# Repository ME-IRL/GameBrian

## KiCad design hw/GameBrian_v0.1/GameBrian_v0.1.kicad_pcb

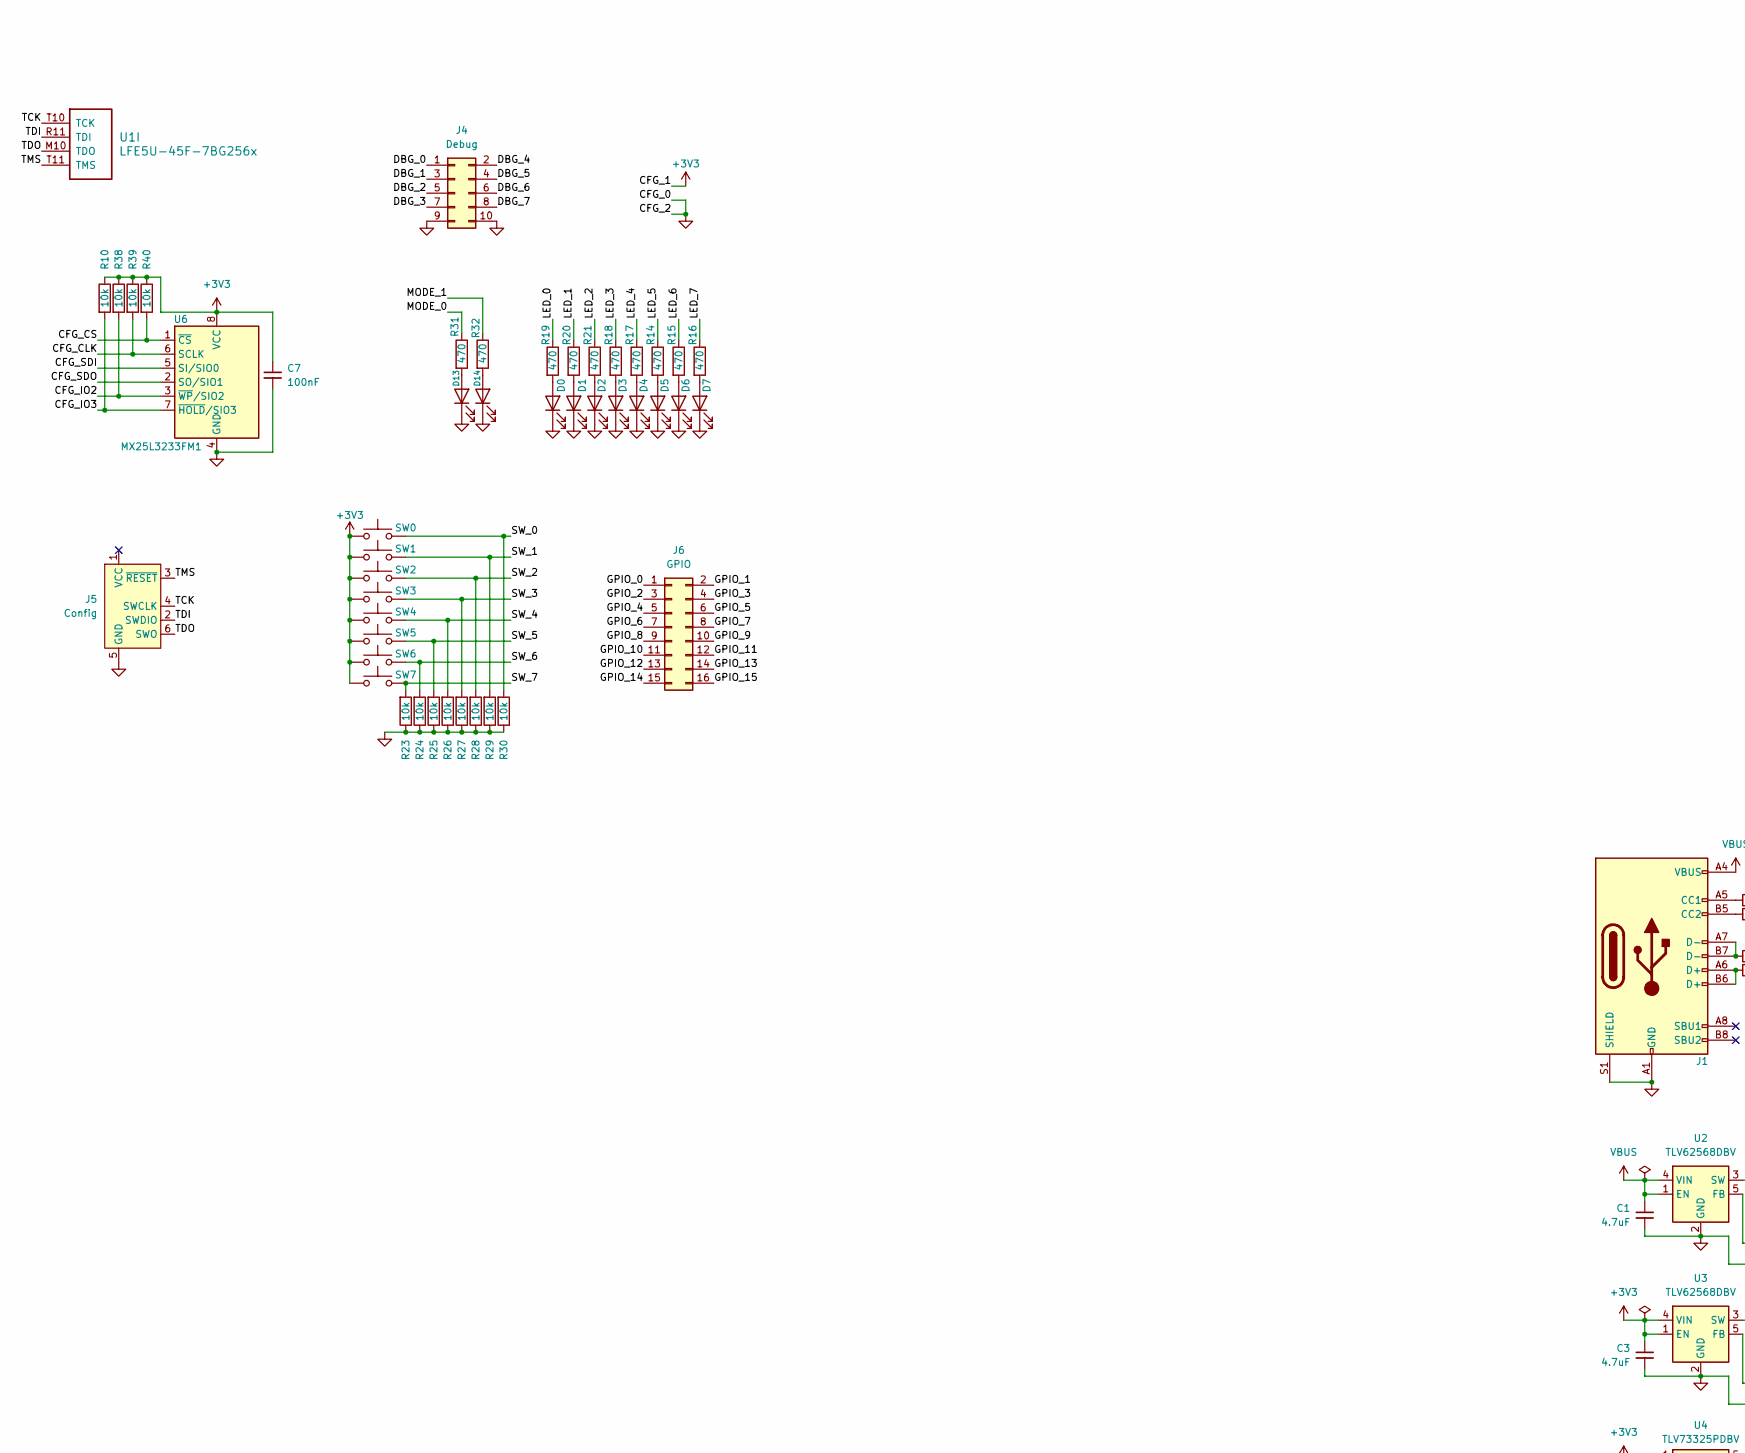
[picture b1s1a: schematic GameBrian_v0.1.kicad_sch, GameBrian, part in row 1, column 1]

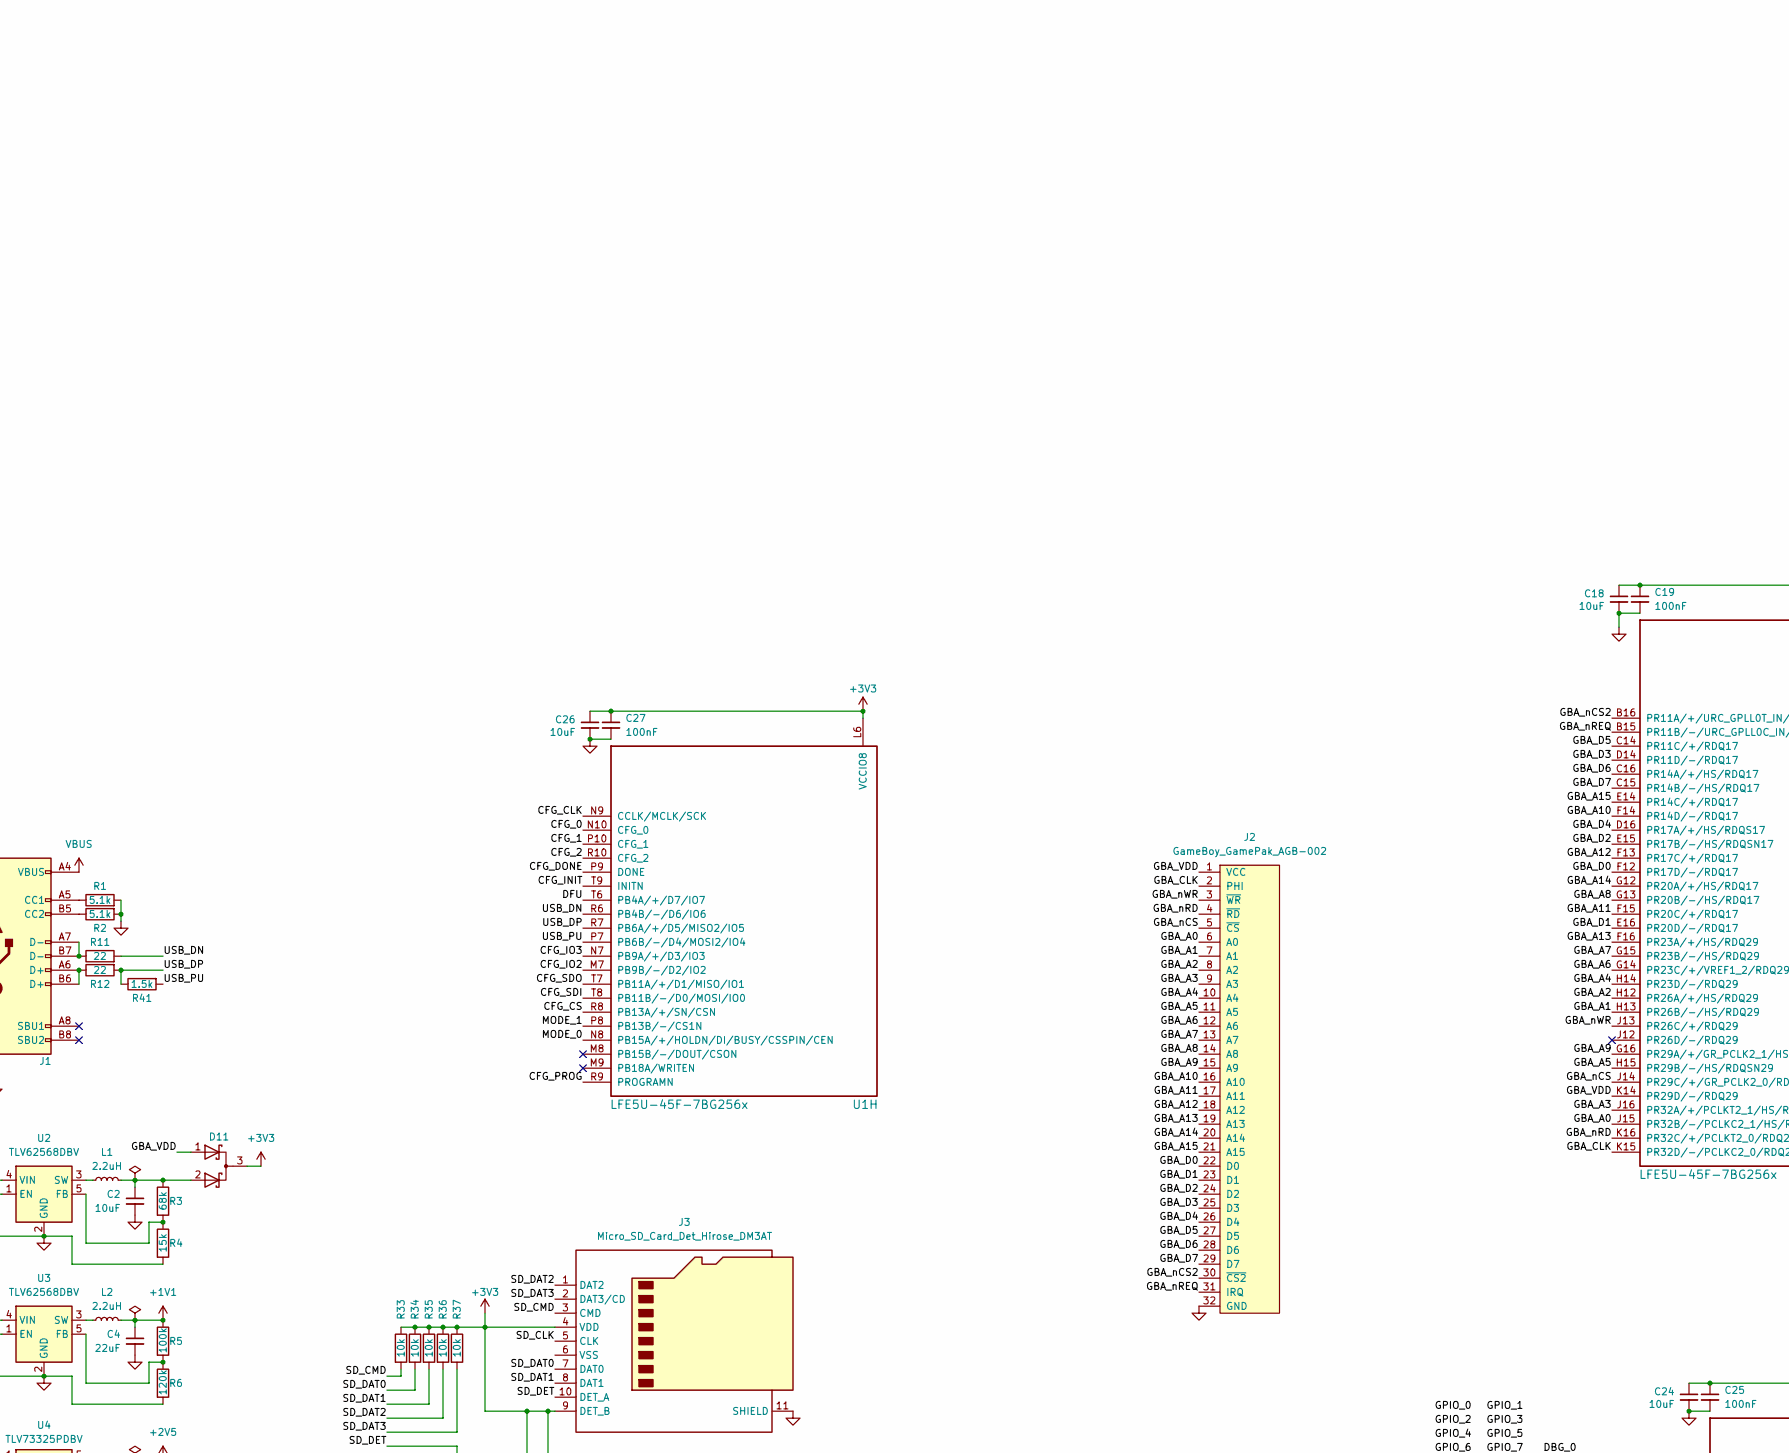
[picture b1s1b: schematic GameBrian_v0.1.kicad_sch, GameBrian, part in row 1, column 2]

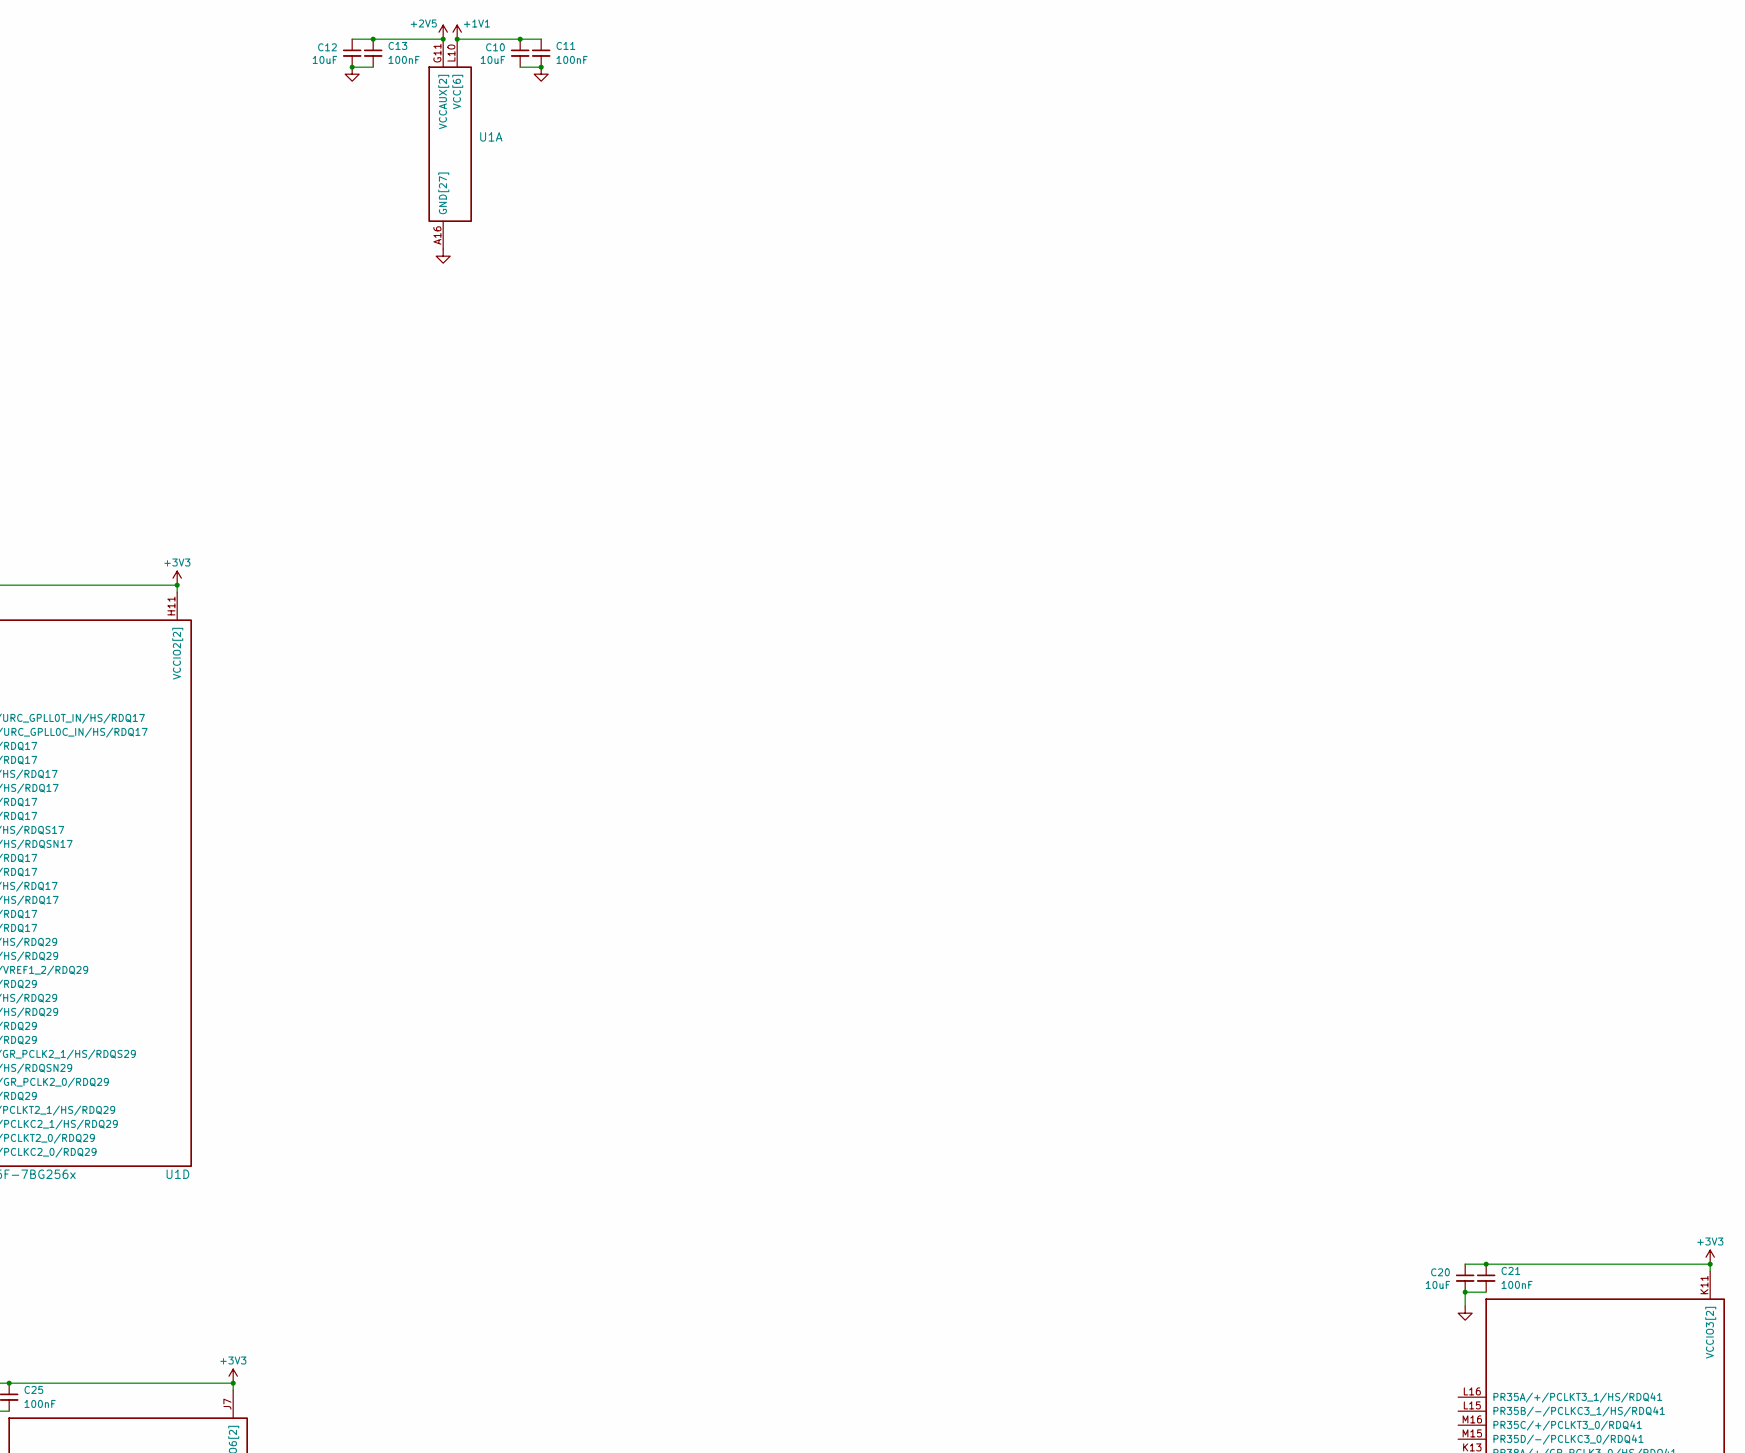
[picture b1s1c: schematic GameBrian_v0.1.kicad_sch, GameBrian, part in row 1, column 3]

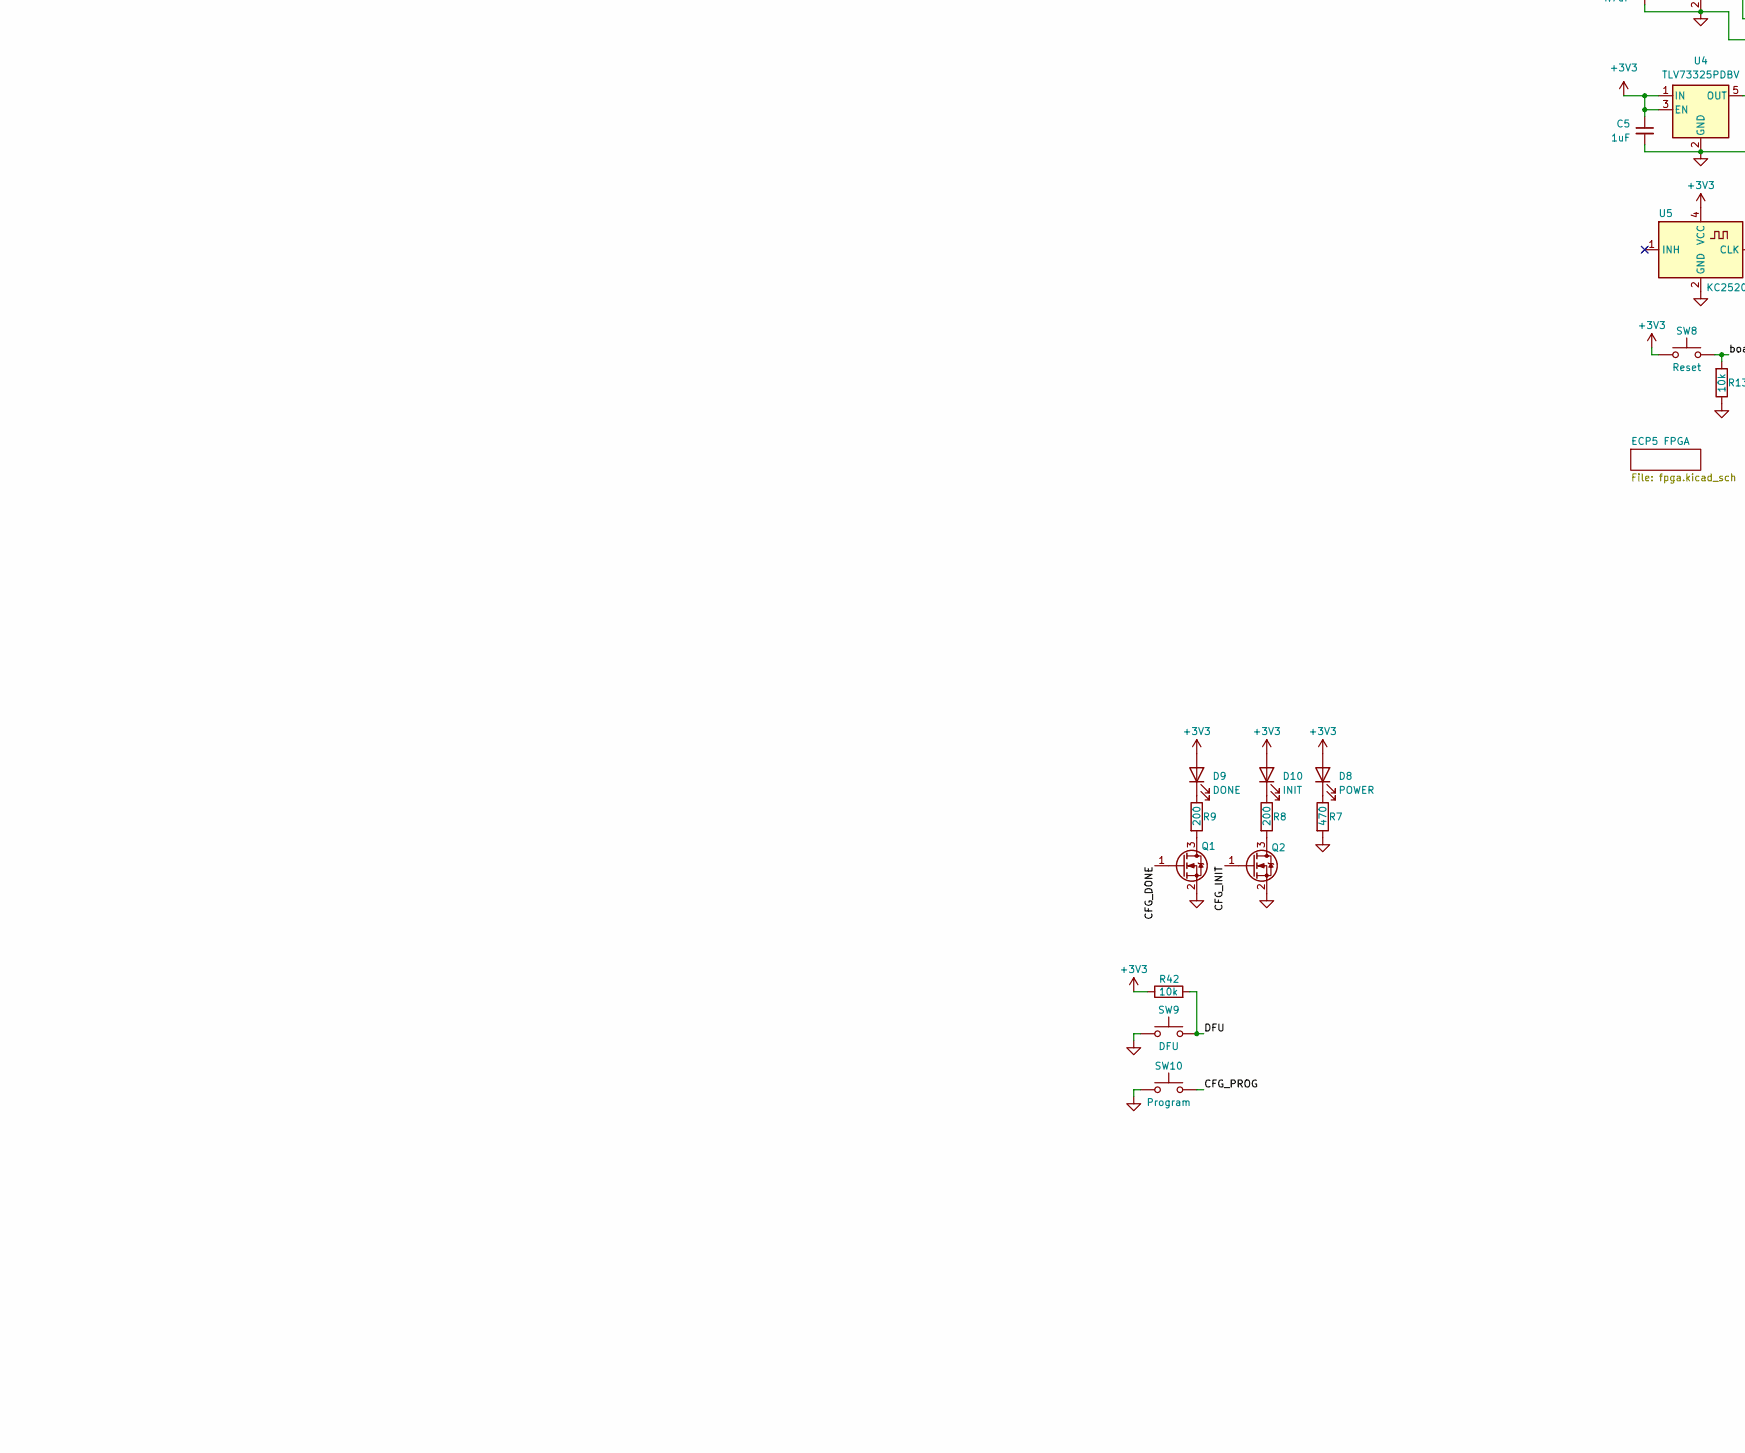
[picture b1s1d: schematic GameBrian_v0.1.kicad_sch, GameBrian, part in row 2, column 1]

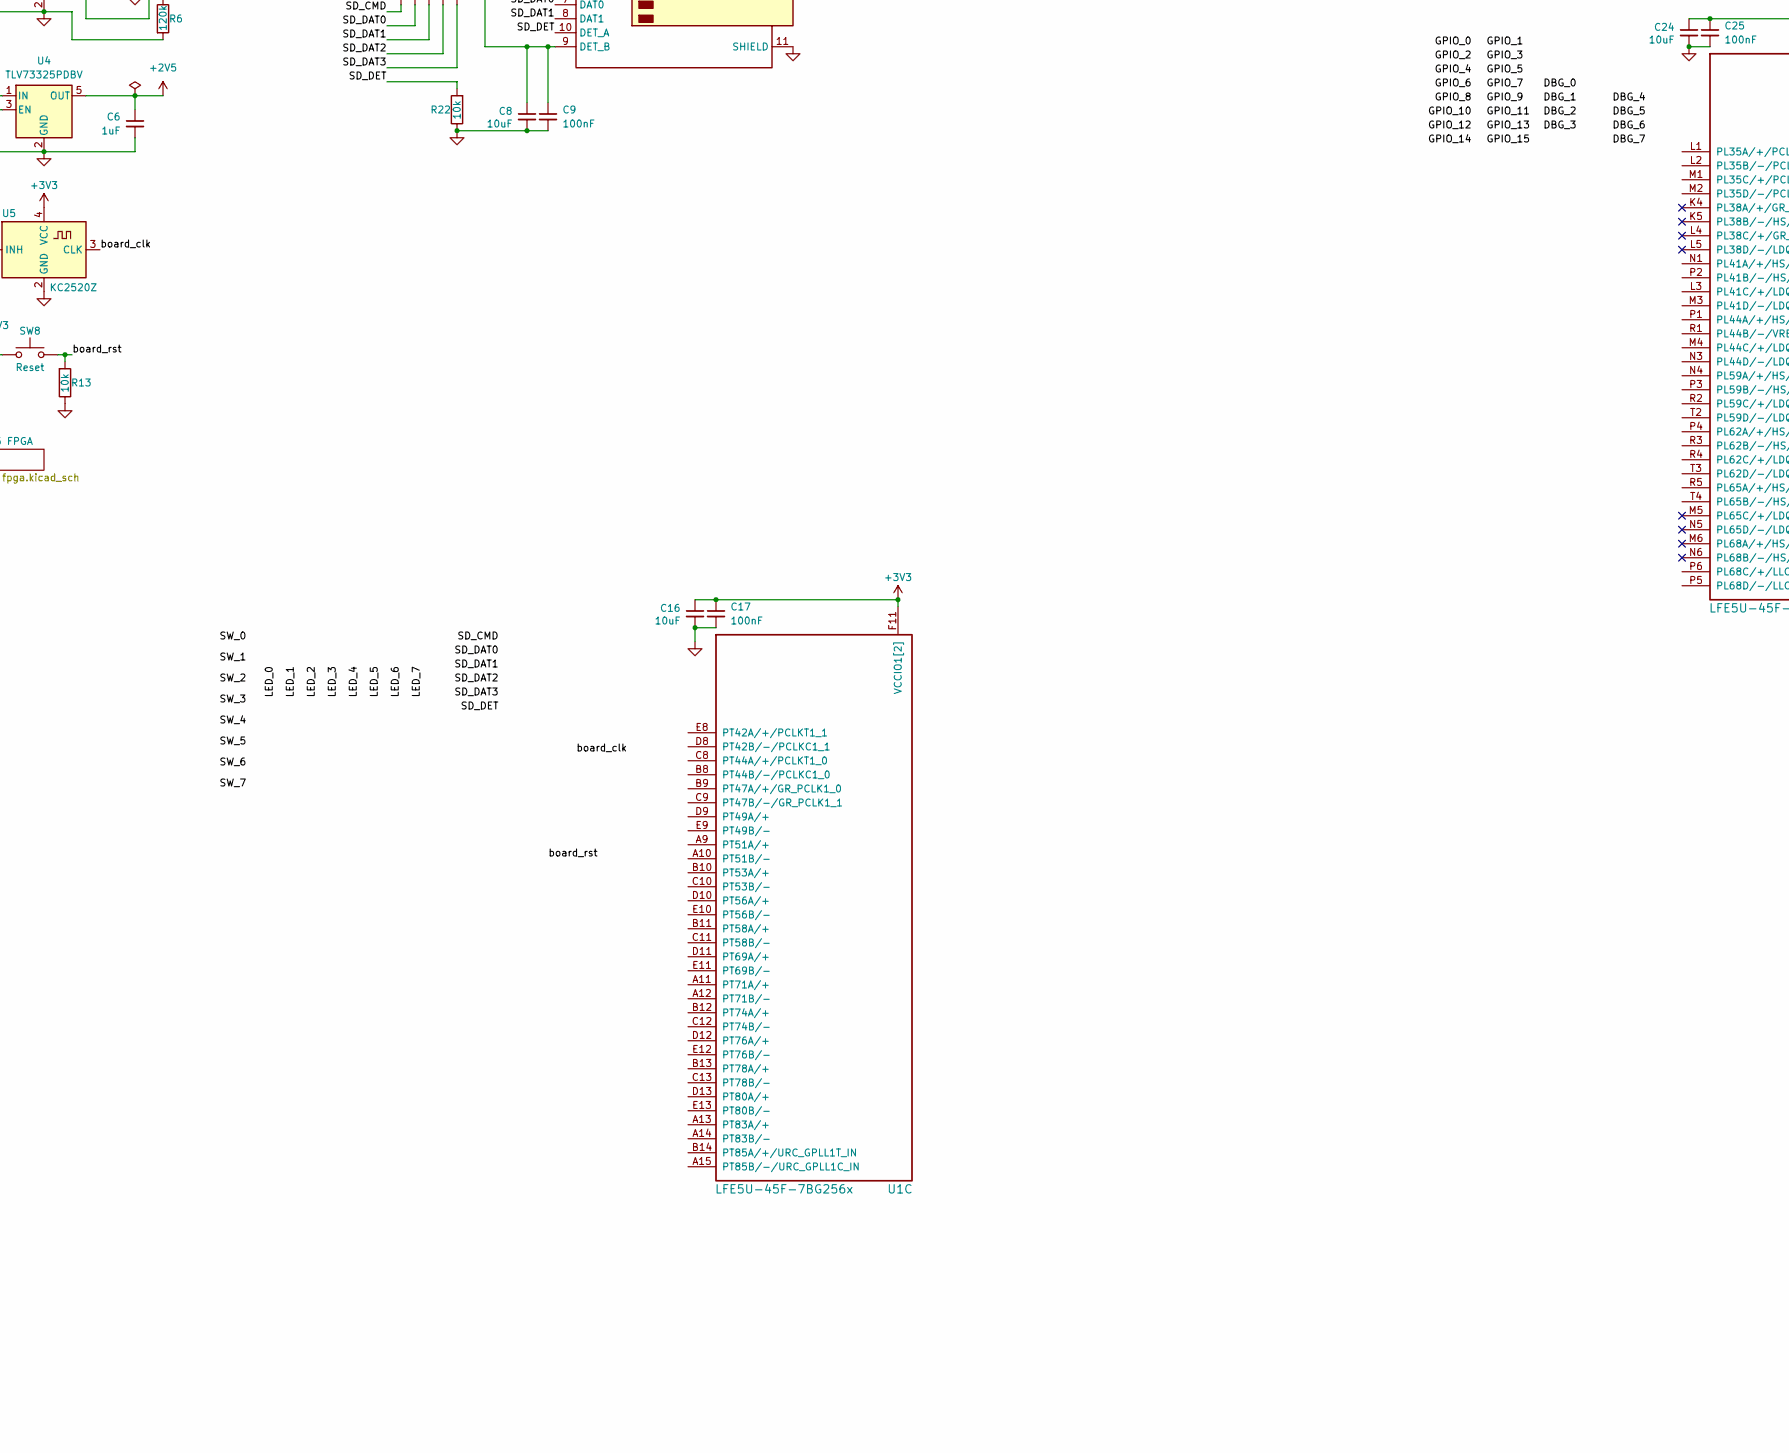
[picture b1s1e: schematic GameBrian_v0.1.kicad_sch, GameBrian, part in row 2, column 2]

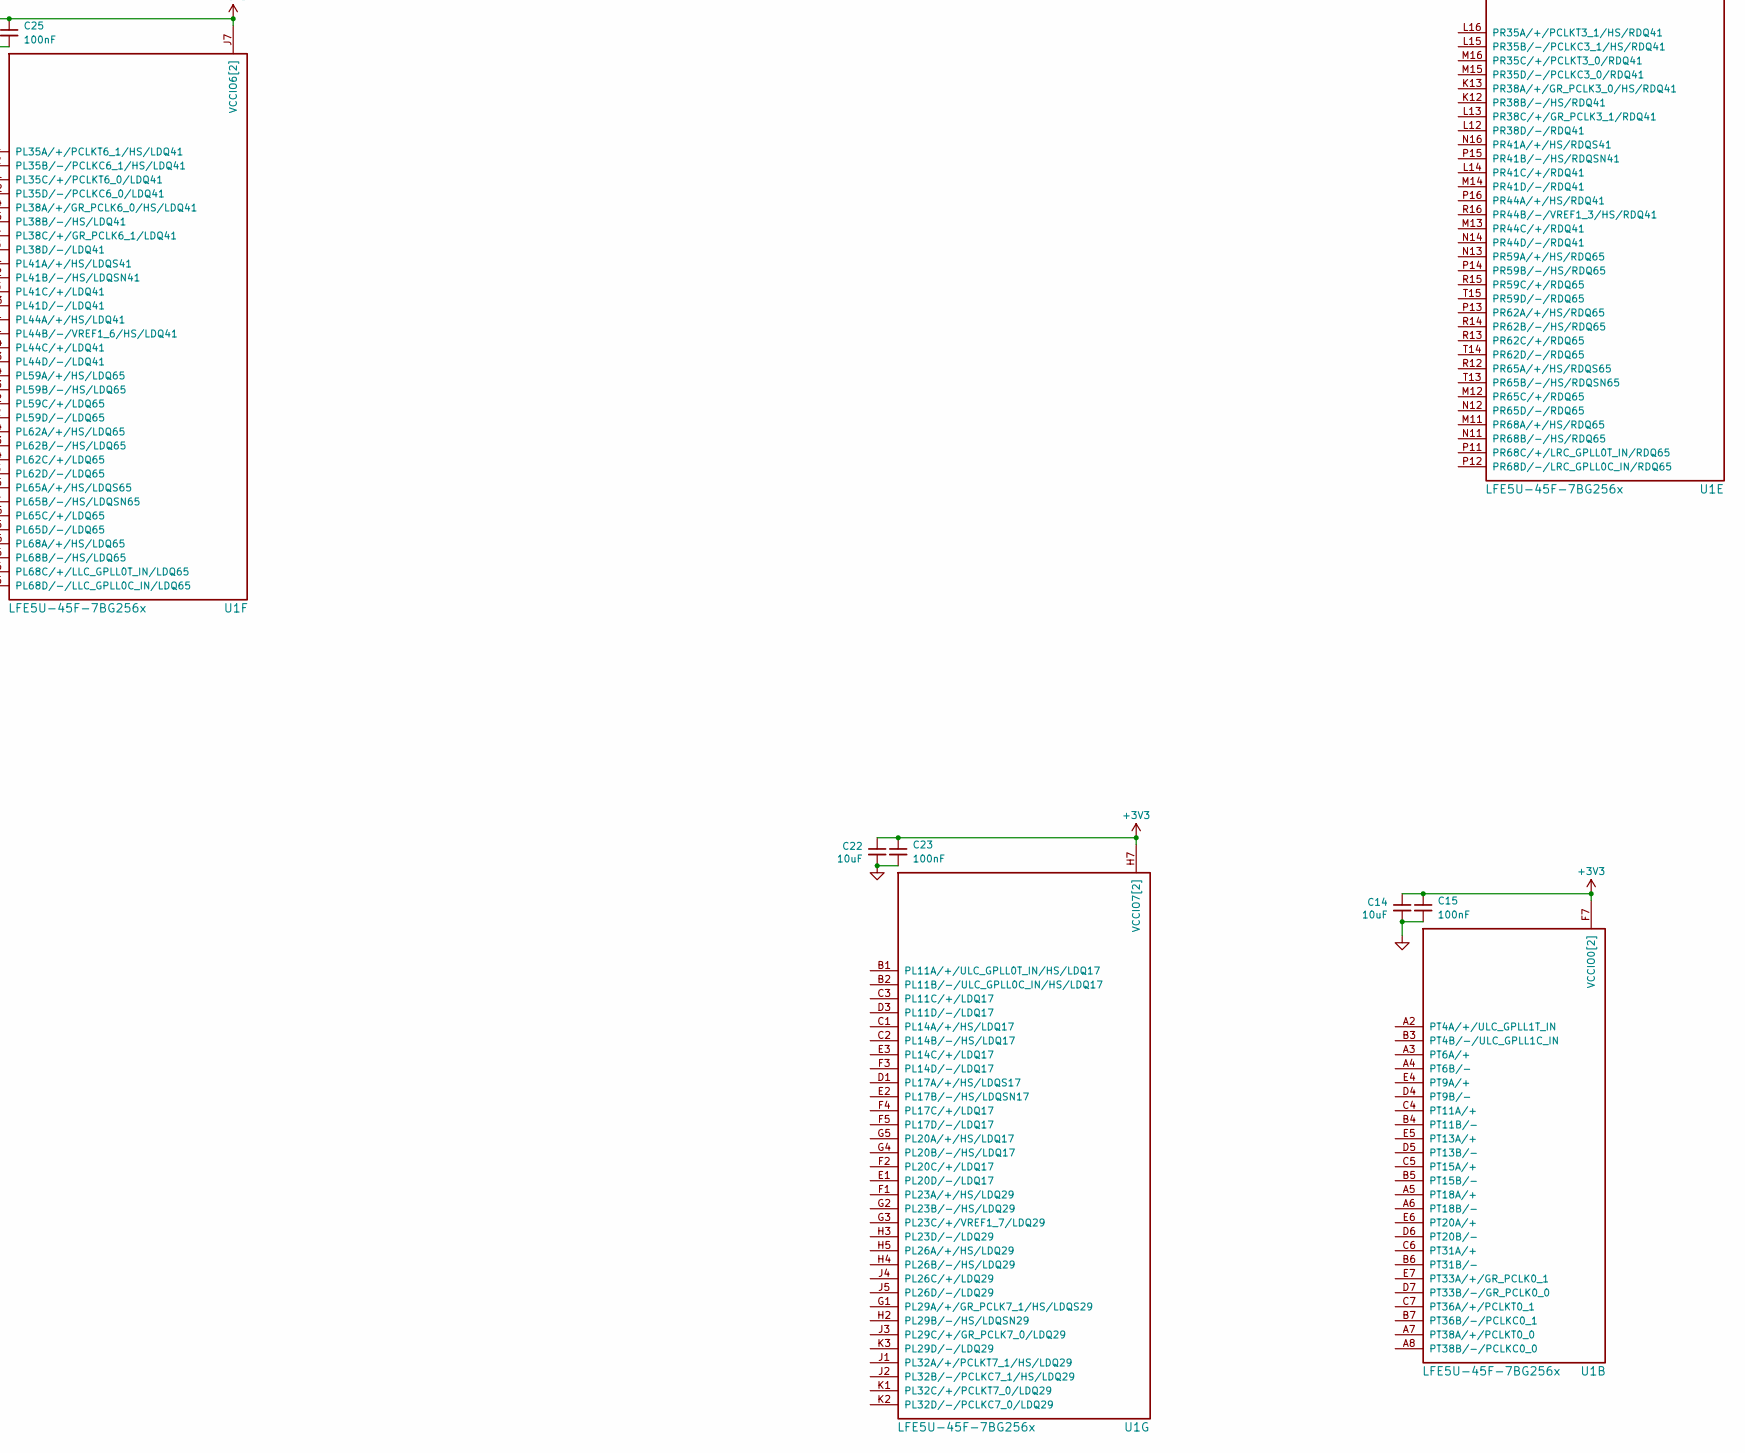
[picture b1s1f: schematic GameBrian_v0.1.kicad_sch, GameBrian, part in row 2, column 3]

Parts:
C1, C3: 4.7uF; C_0603_1608Metric; DIGIKEY 1276-1044-1-ND
C2, C8, C10, C12, C14, C16, C18, C20, C22, C24, C26: 10uF; C_0402_1005Metric; DIGIKEY 490-GRM155R60J106ME05DCT-ND
C4: 22uF; C_0603_1608Metric; DIGIKEY 490-7612-2-ND
C5, C6: 1uF; C_0603_1608Metric; DIGIKEY 311-1446-1-ND
C7, C9, C11, C13, C15, C17, C19, C21, C23, C25, C27: 100nF; C_0402_1005Metric; DIGIKEY 490-6328-1-ND
D0, D1, D2, D3, D4, D5, D6, D7, D13, D14: LED_0603_1608Metric; DIGIKEY 732-4978-1-ND
D8: POWER; LED_0603_1608Metric; DIGIKEY 732-4978-1-ND
D9: DONE; LED_0603_1608Metric; DIGIKEY 732-4978-1-ND
D10: INIT; LED_0603_1608Metric; DIGIKEY 732-4978-1-ND
D11: D_Schottky_Dual_CommonCathode_AAK_Parallel; SOT1061; DIGIKEY 1727-5212-1-ND
J1: USB_C_Receptacle_USB2.0_16P; USB_C_Receptacle_GCT_USB4105-xx-A_16P_TopMnt_Horizontal; DIGIKEY 2073-USB4105-GF-ACT-ND
J2: GameBoy_GamePak_AGB-002; PinSocket_2x16_P2.54mm_Horizontal
J3: Micro_SD_Card_Det_Hirose_DM3AT; microSD_HC_Hirose_DM3AT-SF-PEJM5; DIGIKEY 26-DM3AT-SF-PEJM5(11)CT-ND
J4: Debug; PinHeader_2x05_P2.54mm_Vertical
J5: Config; Tag-Connect_TC2030-IDC-FP_2x03_P1.27mm_Vertical
J6: GPIO; PinHeader_2x08_P2.54mm_Vertical
L1, L2: 2.2uH; L_Taiyo-Yuden_NR-40xx; DIGIKEY 2037-SDER041H-2R2MSCT-ND
Q1, Q2: Q_NMOS_GSD; SOT-23; DIGIKEY DMG1012UW-7DICT-ND
R1, R2: 5.1k; R_0402_1005Metric; DIGIKEY A126379CT-ND
R3: 68k; R_0402_1005Metric; DIGIKEY 311-68.0KLRCT-ND
R4: 15k; R_0402_1005Metric; DIGIKEY 311-15.0KLRCT-ND
R5: 100k; R_0402_1005Metric; DIGIKEY 311-100KLRCT-ND
R6: 120k; R_0402_1005Metric; DIGIKEY 311-120KLRCT-ND
R7, R14, R15, R16, R17, R18, R19, R20, R21, R31, R32: 470; R_0402_1005Metric; DIGIKEY 311-470LRCT-ND
R8, R9: 200; R_0402_1005Metric; DIGIKEY 311-200LRCT-ND
R10, R13, R22, R23, R24, R25, R26, R27, R28, R29, R30, R33, R34, R35, R36, R37, R38, R39, R40, R42: 10k; R_0402_1005Metric; DIGIKEY 311-10KJRCT-ND
R11, R12: 22; R_0402_1005Metric; DIGIKEY 311-22.0LRCT-ND
R41: 1.5k; R_0402_1005Metric; DIGIKEY YAG1380CT-ND
SW0, SW1, SW2, SW3, SW4, SW5, SW6, SW7: SW_SPST_PTS647_Sx50; DIGIKEY PTS647SN50SMTR2LFSCT-ND
SW8: Reset; SW_SPST_PTS647_Sx50; DIGIKEY PTS647SN50SMTR2LFSCT-ND
SW9: DFU; SW_SPST_PTS647_Sx50; DIGIKEY PTS647SN50SMTR2LFSCT-ND
SW10: Program; SW_SPST_PTS647_Sx50; DIGIKEY PTS647SN50SMTR2LFSCT-ND
U1: LFE5U-45F-7BG256x; BGA-256_14.0x14.0mm_Layout16x16_P0.8mm_Ball0.45mm_Pad0.32mm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; DIGIKEY LFE5U-45F-7BG256C-ND
U2, U3: TLV62568DBV; SOT-23-5; DIGIKEY 296-47359-1-ND
U4: TLV73325PDBV; SOT-23-5; DIGIKEY 296-40671-1-ND
U5: KC2520Z; Oscillator_SMD_Kyocera_KC2520Z-4Pin_2.5x2.0mm; DIGIKEY 478-KC2520Z100.000C15XXKCT-ND
U6: MX25L3233FM1; SOP-8_3.9x4.9mm_P1.27mm; DIGIKEY 1092-1221-ND

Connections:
+1V1: C4.1, C10.1, C11.1, L2.2, R5.1, U1.G6 (VCC[6]), U1.G7 (VCC[6]), U1.G9 (VCC[6]), U1.L8 (VCC[6]), U1.L9 (VCC[6]), U1.L10 (VCC[6])
+2V5: C6.1, C12.1, C13.1, U1.G11 (VCCAUX[2]), U1.L7 (VCCAUX[2]), U4.5 (OUT)
+3V3: C3.1, C5.1, C7.1, C8.1, C9.1, C14.1, C15.1, C16.1, C17.1, C18.1, C19.1, C20.1, C21.1, C22.1, C23.1, C24.1, C25.1, C26.1, C27.1, D8.2 (A), D9.2 (A), D10.2 (A), D11.3 (A), J3.4 (VDD), J3.9 (DET_B), R10.1, R33.1, R34.1, R35.1, R36.1, R37.1, R38.1, R39.1, R40.1, R42.1, SW0.1, SW1.1, SW2.1, SW3.1, SW4.1, SW5.1, SW6.1, SW7.1, SW8.2, U1.F6 (VCCIO0[2]), U1.F7 (VCCIO0[2]), U1.F10 (VCCIO1[2]), U1.F11 (VCCIO1[2]), U1.H6 (VCCIO7[2]), U1.H7 (VCCIO7[2]), U1.H11 (VCCIO2[2]), U1.J6 (VCCIO6[2]), U1.J7 (VCCIO6[2]), U1.J11 (VCCIO2[2]), U1.K11 (VCCIO3[2]), U1.L6 (VCCIO8), U1.L11 (VCCIO3[2]), U1.P10 (CFG_1), U3.1 (EN), U3.4 (VIN), U4.1 (IN), U4.3 (EN), U5.4 (VCC), U6.8 (VCC)
/CFG_CLK: R39.2, U1.N9 (CCLK/MCLK/SCK), U6.6 (SCLK)
/CFG_CS: R40.2, U1.R8 (PB13A/+/SN/CSN), U6.1 (~CS)
/CFG_DONE: Q1.1 (G), U1.P9 (DONE)
/CFG_INIT: Q2.1 (G), U1.T9 (INITN)
/CFG_IO2: R38.2, U1.M7 (PB9B/-/D2/IO2), U6.3 (~WP/SIO2)
/CFG_IO3: R10.2, U1.N7 (PB9A/+/D3/IO3), U6.7 (~HOLD/SIO3)
/CFG_PROG: SW10.1, U1.R9 (PROGRAMN)
/CFG_SDI: U1.T8 (PB11B/-/D0/MOSI/IO0), U6.5 (SI/SIO0)
/CFG_SDO: U1.T7 (PB11A/+/D1/MISO/IO1), U6.2 (SO/SIO1)
/DBG_0: J4.1
/DBG_1: J4.3
/DBG_2: J4.5
/DBG_3: J4.7
/DBG_4: J4.2
/DBG_5: J4.4
/DBG_6: J4.6
/DBG_7: J4.8
/DFU: R42.2, SW9.1, U1.T6 (PB4A/+/D7/IO7)
/GBA_A0: J2.6 (A0), U1.J15 (PR32B/-/PCLKC2_1/HS/RDQ29)
/GBA_A1: J2.7 (A1), U1.H13 (PR26B/-/HS/RDQ29)
/GBA_A2: J2.8 (A2), U1.H12 (PR26A/+/HS/RDQ29)
/GBA_A3: J2.9 (A3), U1.J16 (PR32A/+/PCLKT2_1/HS/RDQ29)
/GBA_A4: J2.10 (A4), U1.H14 (PR23D/-/RDQ29)
/GBA_A5: J2.11 (A5), U1.H15 (PR29B/-/HS/RDQSN29)
/GBA_A6: J2.12 (A6), U1.G14 (PR23C/+/VREF1_2/RDQ29)
/GBA_A7: J2.13 (A7), U1.G15 (PR23B/-/HS/RDQ29)
/GBA_A8: J2.14 (A8), U1.G13 (PR20B/-/HS/RDQ17)
/GBA_A9: J2.15 (A9), U1.G16 (PR29A/+/GR_PCLK2_1/HS/RDQS29)
/GBA_A10: J2.16 (A10), U1.F14 (PR14D/-/RDQ17)
/GBA_A11: J2.17 (A11), U1.F15 (PR20C/+/RDQ17)
/GBA_A12: J2.18 (A12), U1.F13 (PR17C/+/RDQ17)
/GBA_A13: J2.19 (A13), U1.F16 (PR23A/+/HS/RDQ29)
/GBA_A14: J2.20 (A14), U1.G12 (PR20A/+/HS/RDQ17)
/GBA_A15: J2.21 (A15), U1.E14 (PR14C/+/RDQ17)
/GBA_CLK: J2.2 (PHI), U1.K15 (PR32D/-/PCLKC2_0/RDQ29)
/GBA_D0: J2.22 (D0), U1.F12 (PR17D/-/RDQ17)
/GBA_D1: J2.23 (D1), U1.E16 (PR20D/-/RDQ17)
/GBA_D2: J2.24 (D2), U1.E15 (PR17B/-/HS/RDQSN17)
/GBA_D3: J2.25 (D3), U1.D14 (PR11D/-/RDQ17)
/GBA_D4: J2.26 (D4), U1.D16 (PR17A/+/HS/RDQS17)
/GBA_D5: J2.27 (D5), U1.C14 (PR11C/+/RDQ17)
/GBA_D6: J2.28 (D6), U1.C16 (PR14A/+/HS/RDQ17)
/GBA_D7: J2.29 (D7), U1.C15 (PR14B/-/HS/RDQ17)
/GBA_VDD: D11.1 (K), J2.1 (VCC), U1.K14 (PR29D/-/RDQ29)
/GBA_nCS: J2.5 (~CS), U1.J14 (PR29C/+/GR_PCLK2_0/RDQ29)
/GBA_nCS2: J2.30 (~CS2), U1.B16 (PR11A/+/URC_GPLL0T_IN/HS/RDQ17)
/GBA_nRD: J2.4 (~RD), U1.K16 (PR32C/+/PCLKT2_0/RDQ29)
/GBA_nREQ: J2.31 (IRQ), U1.B15 (PR11B/-/URC_GPLL0C_IN/HS/RDQ17)
/GBA_nWR: J2.3 (~WR), U1.J13 (PR26C/+/RDQ29)
/GPIO_0: J6.1
/GPIO_1: J6.2
/GPIO_2: J6.3
/GPIO_3: J6.4
/GPIO_4: J6.5
/GPIO_5: J6.6
/GPIO_6: J6.7
/GPIO_7: J6.8
/GPIO_8: J6.9
/GPIO_9: J6.10
/GPIO_10: J6.11
/GPIO_11: J6.12
/GPIO_12: J6.13
/GPIO_13: J6.14
/GPIO_14: J6.15
/GPIO_15: J6.16
/LED_0: R19.1
/LED_1: R20.1
/LED_2: R21.1
/LED_3: R18.1
/LED_4: R17.1
/LED_5: R14.1
/LED_6: R15.1
/LED_7: R16.1
/MODE_0: R31.1, U1.N8 (PB15A/+/HOLDN/DI/BUSY/CSSPIN/CEN)
/MODE_1: R32.1, U1.P8 (PB13B/-/CS1N)
/SD_CLK: J3.5 (CLK)
/SD_CMD: J3.3 (CMD), R33.2
/SD_DAT0: J3.7 (DAT0), R34.2
/SD_DAT1: J3.8 (DAT1), R35.2
/SD_DAT2: J3.1 (DAT2), R36.2
/SD_DAT3: J3.2 (DAT3/CD), R37.2
/SD_DET: J3.10 (DET_A), R22.2
/SW_0: R30.2, SW0.2
/SW_1: R29.2, SW1.2
/SW_2: R28.2, SW2.2
/SW_3: R27.2, SW3.2
/SW_4: R26.2, SW4.2
/SW_5: R25.2, SW5.2
/SW_6: R24.2, SW6.2
/SW_7: R23.2, SW7.2
/TCK: J5.4 (SWCLK), U1.T10 (TCK)
/TDI: J5.2 (SWDIO), U1.R11 (TDI)
/TDO: J5.6 (SWO), U1.M10 (TDO)
/TMS: J5.3 (~RESET), U1.T11 (TMS)
/USB_DN: R11.2, U1.R6 (PB4B/-/D6/IO6)
/USB_DP: R12.2, R41.1, U1.R7 (PB6A/+/D5/MISO2/IO5)
/USB_PU: R41.2, U1.P7 (PB6B/-/D4/MOSI2/IO4)
/board_clk: U5.3 (CLK)
/board_rst: R13.2, SW8.1
GND: C1.2, C2.2, C3.2, C4.2, C5.2, C6.2, C7.2, C8.2, C9.2, C10.2, C11.2, C12.2, C13.2, C14.2, C15.2, C16.2, C17.2, C18.2, C19.2, C20.2, C21.2, C22.2, C23.2, C24.2, C25.2, C26.2, C27.2, D0.1 (K), D1.1 (K), D2.1 (K), D3.1 (K), D4.1 (K), D5.1 (K), D6.1 (K), D7.1 (K), D13.1 (K), D14.1 (K), J1.A1 (GND), J1.A12 (GND), J1.B1 (GND), J1.B12 (GND), J1.S1 (SHIELD), J2.32 (GND), J3.11 (SHIELD), J4.9, J4.10, J5.5 (GND), Q1.2 (S), Q2.2 (S), R1.2, R2.2, R4.2, R6.2, R7.2, R13.1, R22.1, R23.1, R24.1, R25.1, R26.1, R27.1, R28.1, R29.1, R30.1, SW9.2, SW10.2, U1.A1 (GND[27]), U1.A16 (GND[27]), U1.D2 (GND[27]), U1.D15 (GND[27]), U1.F8 (GND[27]), U1.F9 (GND[27]), U1.G8 (GND[27]), U1.G10 (GND[27]), U1.H1 (GND[27]), U1.H8 (GND[27]), U1.H9 (GND[27]), U1.H10 (GND[27]), U1.H16 (GND[27]), U1.J8 (GND[27]), U1.J9 (GND[27]), U1.J10 (GND[27]), U1.K6 (GND[27]), U1.K7 (GND[27]), U1.K8 (GND[27]), U1.K9 (GND[27]), U1.K10 (GND[27]), U1.N2 (GND[27]), U1.N10 (CFG_0), U1.N15 (GND[27]), U1.R10 (CFG_2), U1.T1 (GND[27]), U1.T5 (GND[27]), U1.T12 (GND[27]), U1.T16 (GND[27]), U2.2 (GND), U3.2 (GND), U4.2 (GND), U5.2 (GND), U6.4 (GND)
unnamed: C2.1, D11.2 (K), L1.2, R3.1
unnamed: D0.2 (A), R19.2
unnamed: D1.2 (A), R20.2
unnamed: D2.2 (A), R21.2
unnamed: D3.2 (A), R18.2
unnamed: D4.2 (A), R17.2
unnamed: D5.2 (A), R14.2
unnamed: D6.2 (A), R15.2
unnamed: D7.2 (A), R16.2
unnamed: D8.1 (K), R7.1
unnamed: D9.1 (K), R9.1
unnamed: D10.1 (K), R8.1
unnamed: D13.2 (A), R31.2
unnamed: D14.2 (A), R32.2
unnamed: J1.A5 (CC1), R1.1
unnamed: J1.B5 (CC2), R2.1
unnamed: J1.A6 (D+), J1.B6 (D+), R12.1
unnamed: J1.A7 (D-), J1.B7 (D-), R11.1
unnamed: Q1.3 (D), R9.2
unnamed: Q2.3 (D), R8.2
unnamed: R3.2, R4.1, U2.5 (FB)
unnamed: L1.1, U2.3 (SW)
unnamed: R5.2, R6.1, U3.5 (FB)
unnamed: L2.1, U3.3 (SW)
VBUS: C1.1, J1.A4 (VBUS), J1.A9 (VBUS), J1.B4 (VBUS), J1.B9 (VBUS), U2.1 (EN), U2.4 (VIN)
